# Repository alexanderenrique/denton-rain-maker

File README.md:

# denton-rain-maker

KiCad schematic and PCB for **Denton's Rainmaker** — a desk recirculating water/mist feature.

## Files

- `denton-rain-maker.kicad_pro` — project
- `denton-rain-maker.kicad_sch` — schematic
- `denton-rain-maker.kicad_pcb` — board layout

Open the `.kicad_pro` file in [KiCad](https://www.kicad.org/) 8 or newer.

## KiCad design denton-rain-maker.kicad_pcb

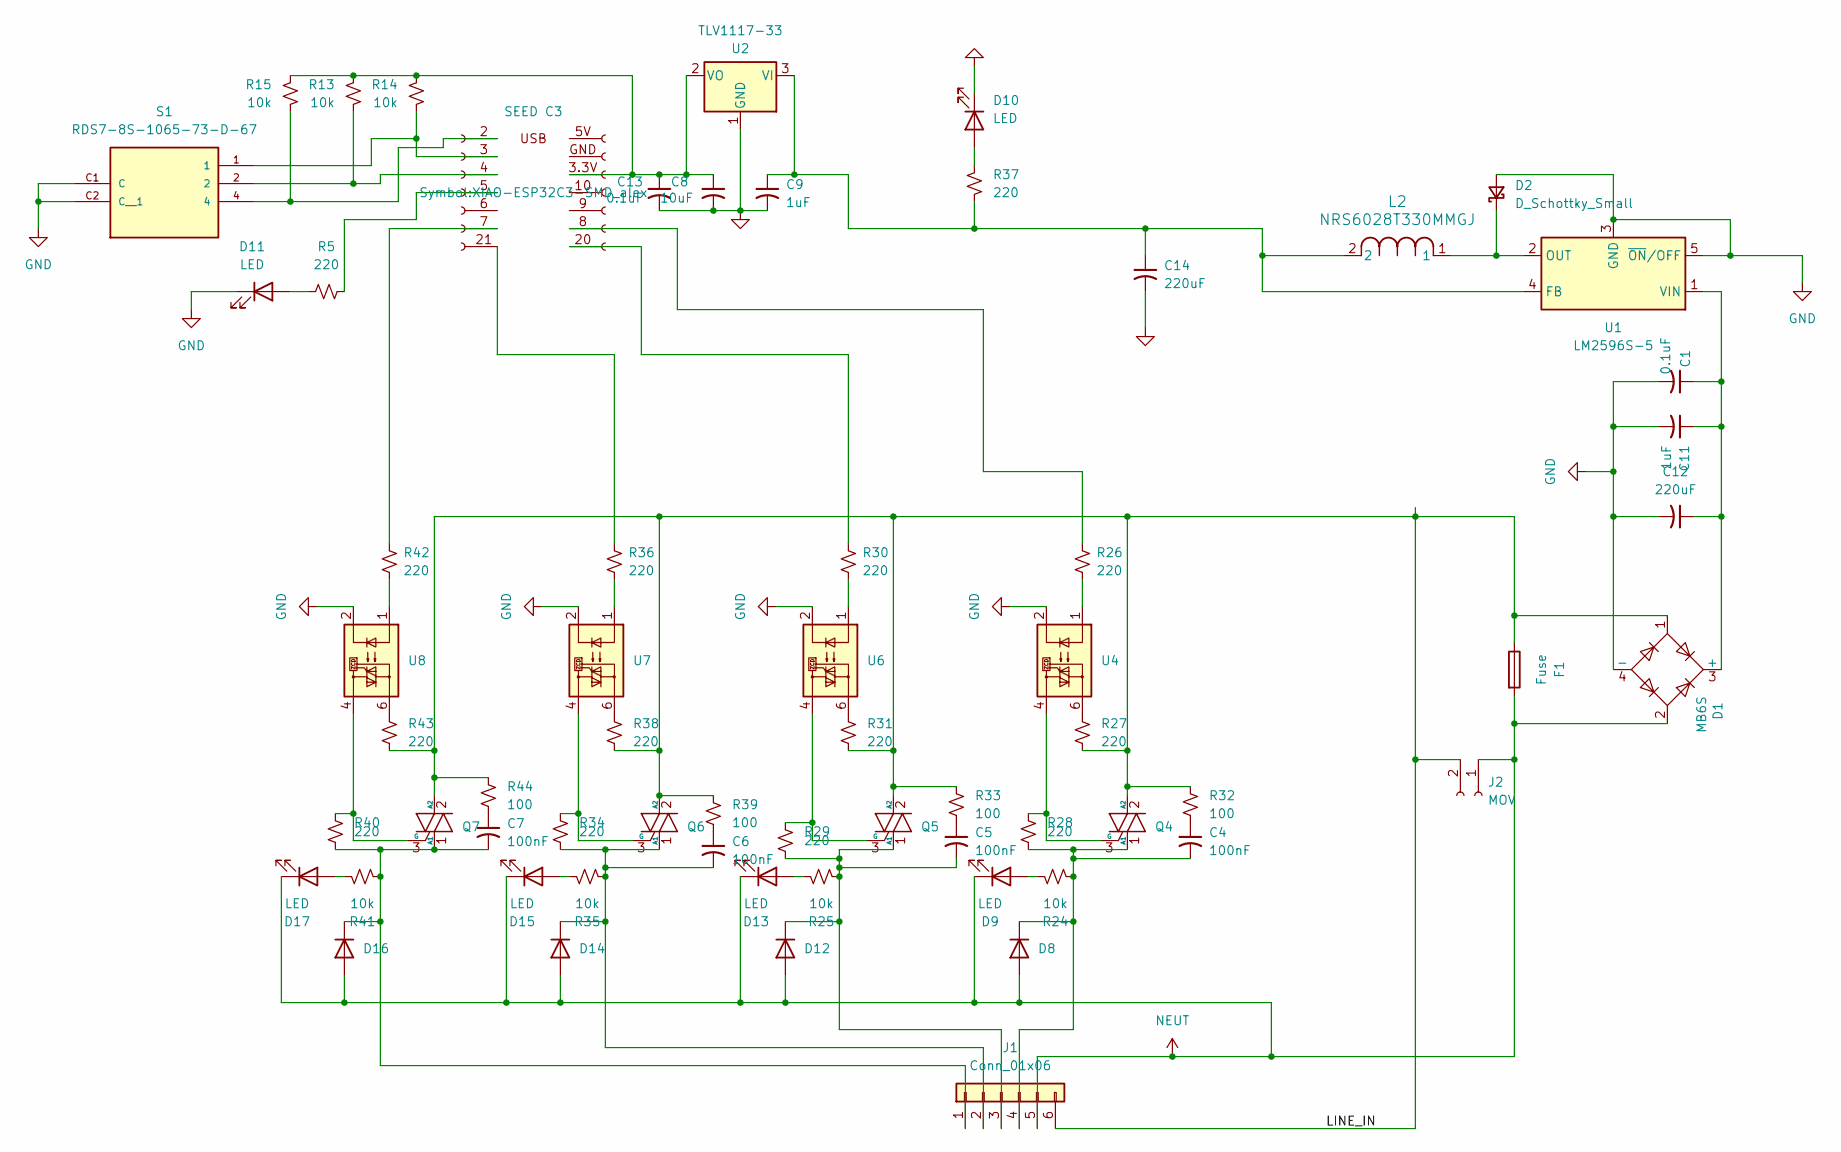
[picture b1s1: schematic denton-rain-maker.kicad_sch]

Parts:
C1, C13: 0.1uF; C_1206_3216Metric_Pad1.33x1.80mm_HandSolder
C4, C5, C6, C7: 100nF; C_1206_3216Metric_Pad1.33x1.80mm_HandSolder
C8: 10uF; C_1206_3216Metric_Pad1.33x1.80mm_HandSolder
C9, C11: 1uF; C_1206_3216Metric_Pad1.33x1.80mm_HandSolder
C12, C14: 220uF; CP_Radial_D10.0mm_P5.00mm
D1: MB6S; TO-269AA
D2: D_Schottky_Small; D_MicroSMP_LargeCathode
D8, D12, D14, D16: 1N4148W; D_SOD-123
D9, D10, D11, D13, D15, D17: LED; LED_D3.0mm
F1: Fuse; Fuseholder_Blade_Mini_Keystone_3568
J1: Conn_01x06; TerminalBlock_Phoenix_MPT-0,5-6-2.54_1x06_P2.54mm_Horizontal
J2: MOV; C_Disc_D7.5mm_W5.0mm_P7.50mm
J3: SEED C3; XIAO-ESP32C3-SMD_alex
L2: NRS6028T330MMGJ; IND_TAIYO_NRS6028_TAY
Q4, Q5, Q6, Q7: BT136S-800E; TO-252-3_TabPin2
R5, R26, R27, R28, R29, R30, R31, R34, R36, R37, R38, R40, R42, R43: 220; R_1206_3216Metric_Pad1.30x1.75mm_HandSolder
R13, R14, R15, R24, R25, R35, R41: 10k; R_1206_3216Metric_Pad1.30x1.75mm_HandSolder
R32, R33, R39, R44: 100; R_1206_3216Metric_Pad1.30x1.75mm_HandSolder
S1: RDS7-8S-1065-73-D-67; SW_RDS7-8S-1065-73-D-67; PARTREV 1.0
U1: LM2596S-5; TO-263-5_TabPin3
U2: TLV1117-33; SOT-223-3_TabPin2
U4, U6, U7, U8: MOC3063M; DIP-6_W7.62mm

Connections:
/LINE_IN: D1.1, F1.1, J1.6, J2.2, Q4.2 (A2), Q5.2 (A2), Q6.2 (A2), Q7.2 (A2), R27.2, R31.2, R32.1, R33.1, R38.2, R39.1, R43.2, R44.1
GND: C1.2, C8.2, C9.2, C11.2, C12.2, C13.2, C14.2, D1.4 (-), D2.2 (A), D10.1 (K), D11.1 (K), S1.C1 (C), S1.C2 (C__1), U1.3 (GND), U1.5 (~ON/OFF), U2.1 (GND), U4.2, U6.2, U7.2, U8.2
NEUT: D1.2, D8.2 (A), D9.1 (K), D12.2 (A), D13.1 (K), D14.2 (A), D15.1 (K), D16.2 (A), D17.1 (K), F1.2, J1.5, J2.1
unnamed: C4.1, R32.2
unnamed: C5.1, R33.2
unnamed: C6.1, R39.2
unnamed: C7.1, R44.2
unnamed: C1.1, C11.1, C12.1, D1.3 (+), U1.1 (VIN)
unnamed: D2.1 (K), L2.1, U1.2 (OUT)
unnamed: C4.2, D8.1 (K), J1.4, Q4.1 (A1), R24.2, R28.2
unnamed: D9.2 (A), R24.1
unnamed: D10.2 (A), R37.1
unnamed: D11.2 (A), R5.1
unnamed: C5.2, D12.1 (K), J1.3, Q5.1 (A1), R25.2, R29.2
unnamed: D13.2 (A), R25.1
unnamed: C6.2, D14.1 (K), J1.2, Q6.1 (A1), R34.2, R35.2
unnamed: D15.2 (A), R35.1
unnamed: C7.2, D16.1 (K), J1.1, Q7.1 (A1), R40.2, R41.2
unnamed: D17.2 (A), R41.1
unnamed: J3.21 (Pin_2), R36.2
unnamed: J3.7 (Pin_3), R42.2
unnamed: J3.5, R5.2
unnamed: J3.4 (Pin_6), R13.2, S1.2
unnamed: J3.8 (Pin_6), R26.2
unnamed: J3.3 (Pin_7), R14.2, S1.1
unnamed: J3.20 (Pin_7), R30.2
unnamed: J3.2 (Pin_8), R15.2, S1.4
unnamed: Q4.3 (G), R28.1, U4.4
unnamed: Q5.3 (G), R29.1, U6.4
unnamed: Q6.3 (G), R34.1, U7.4
unnamed: Q7.3 (G), R40.1, U8.4
unnamed: R26.1, U4.1
unnamed: R27.1, U4.6
unnamed: R30.1, U6.1
unnamed: R31.1, U6.6
unnamed: R36.1, U7.1
unnamed: R38.1, U7.6
unnamed: R42.1, U8.1
unnamed: R43.1, U8.6
unnamed: C9.1, C14.1, L2.2, R37.2, U1.4 (FB), U2.3 (VI)
unnamed: C8.1, C13.1, J3.3.3V (Pin_3), R13.1, R14.1, R15.1, U2.2 (VO)

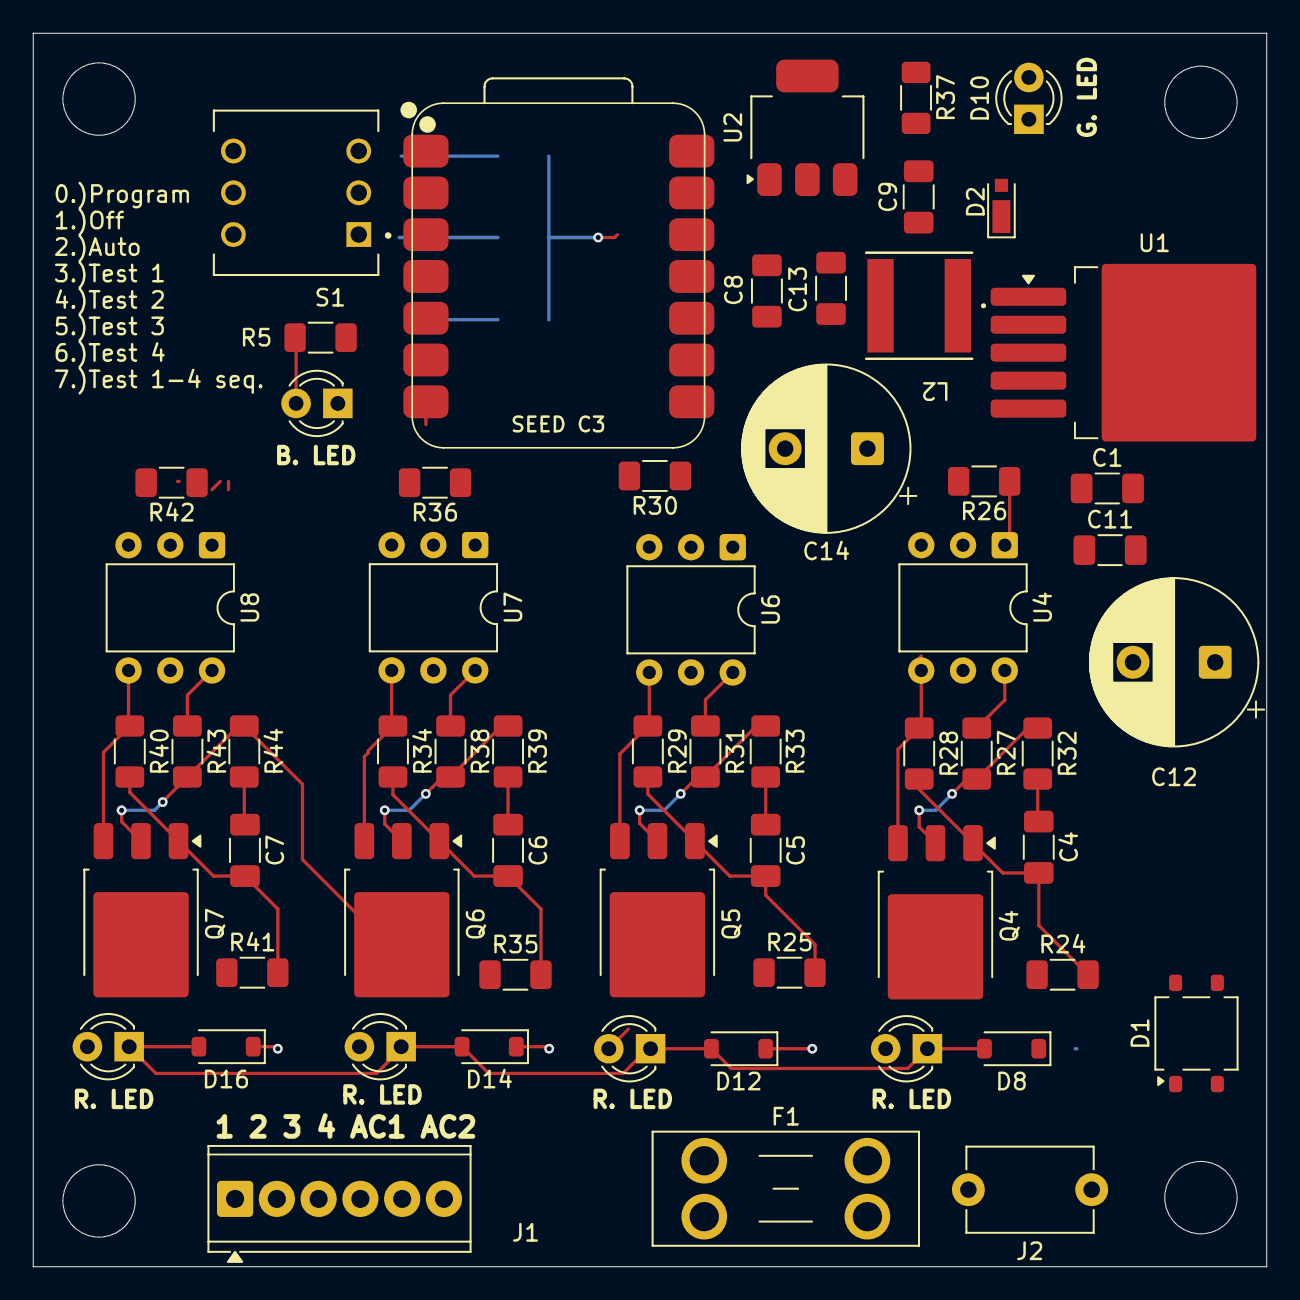
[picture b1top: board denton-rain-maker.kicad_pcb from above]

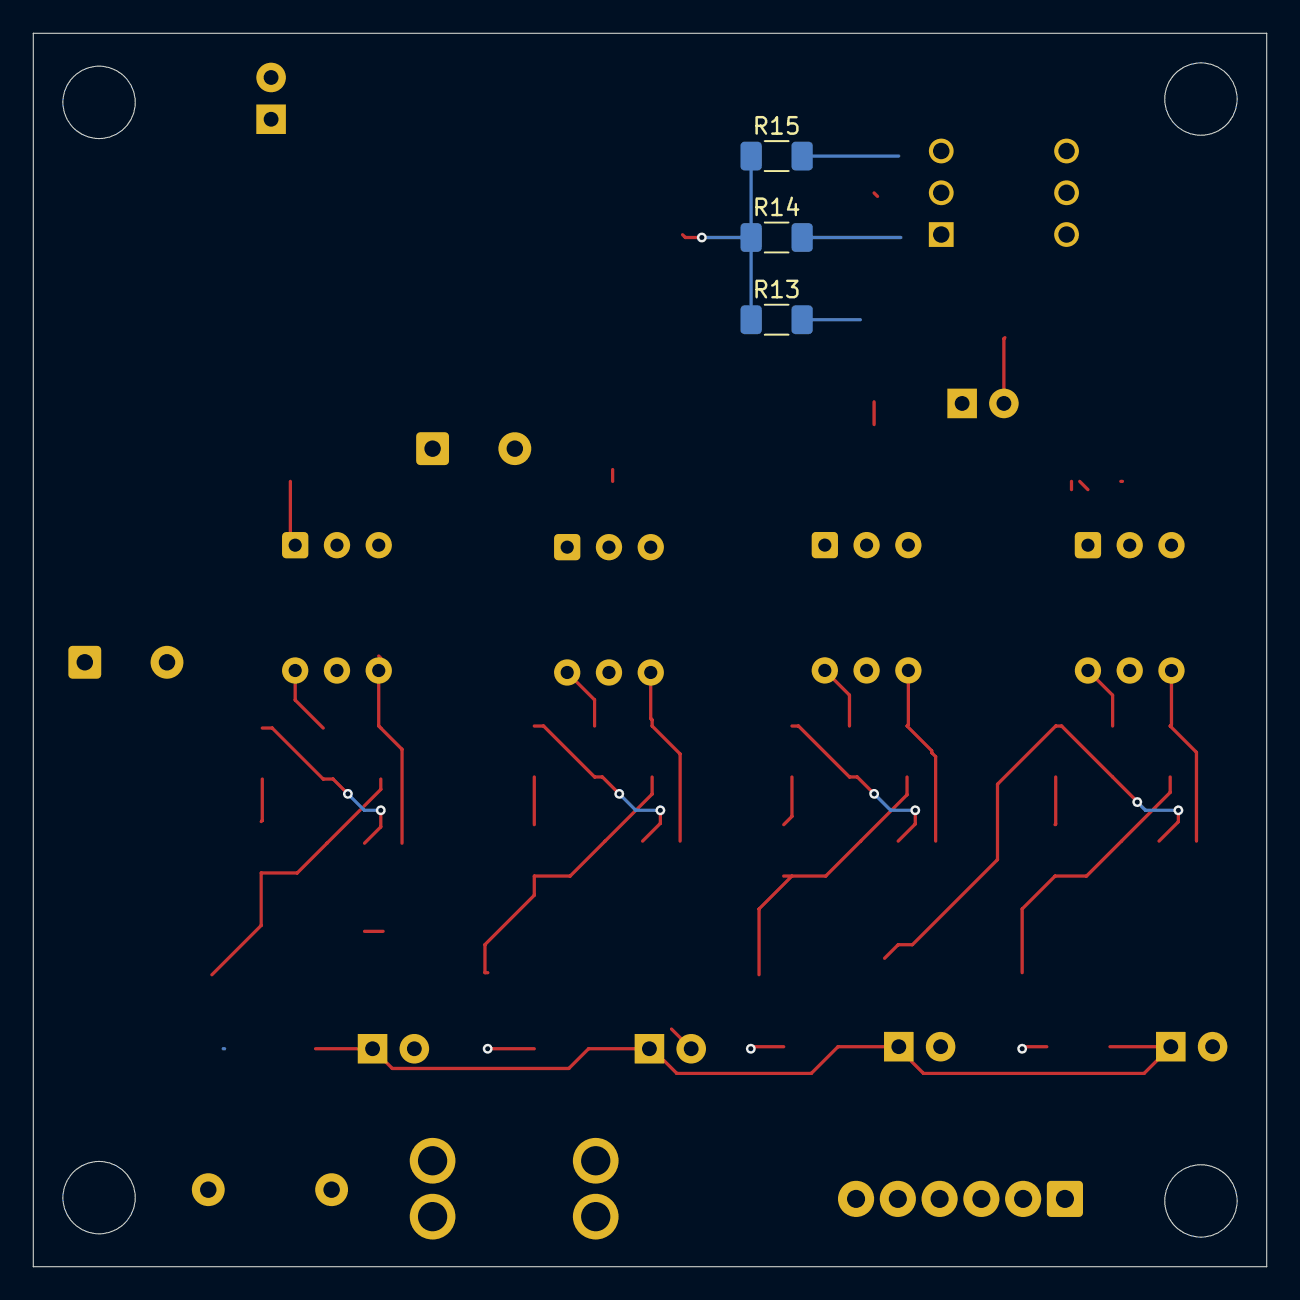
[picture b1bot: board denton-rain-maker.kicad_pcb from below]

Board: 2 copper layers, 75.0 x 75.0 mm, 64 parts (3 on the bottom side), 41 nets.

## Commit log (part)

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2026-06-16 rotary switch checkpoint
2026-06-16 starting on layout
2026-06-16 layout continues
2026-06-16 gotta stop
2026-06-19 remember to change the buck converter
2026-06-20 added LDO,MOV
2026-06-23 new pwr supply
